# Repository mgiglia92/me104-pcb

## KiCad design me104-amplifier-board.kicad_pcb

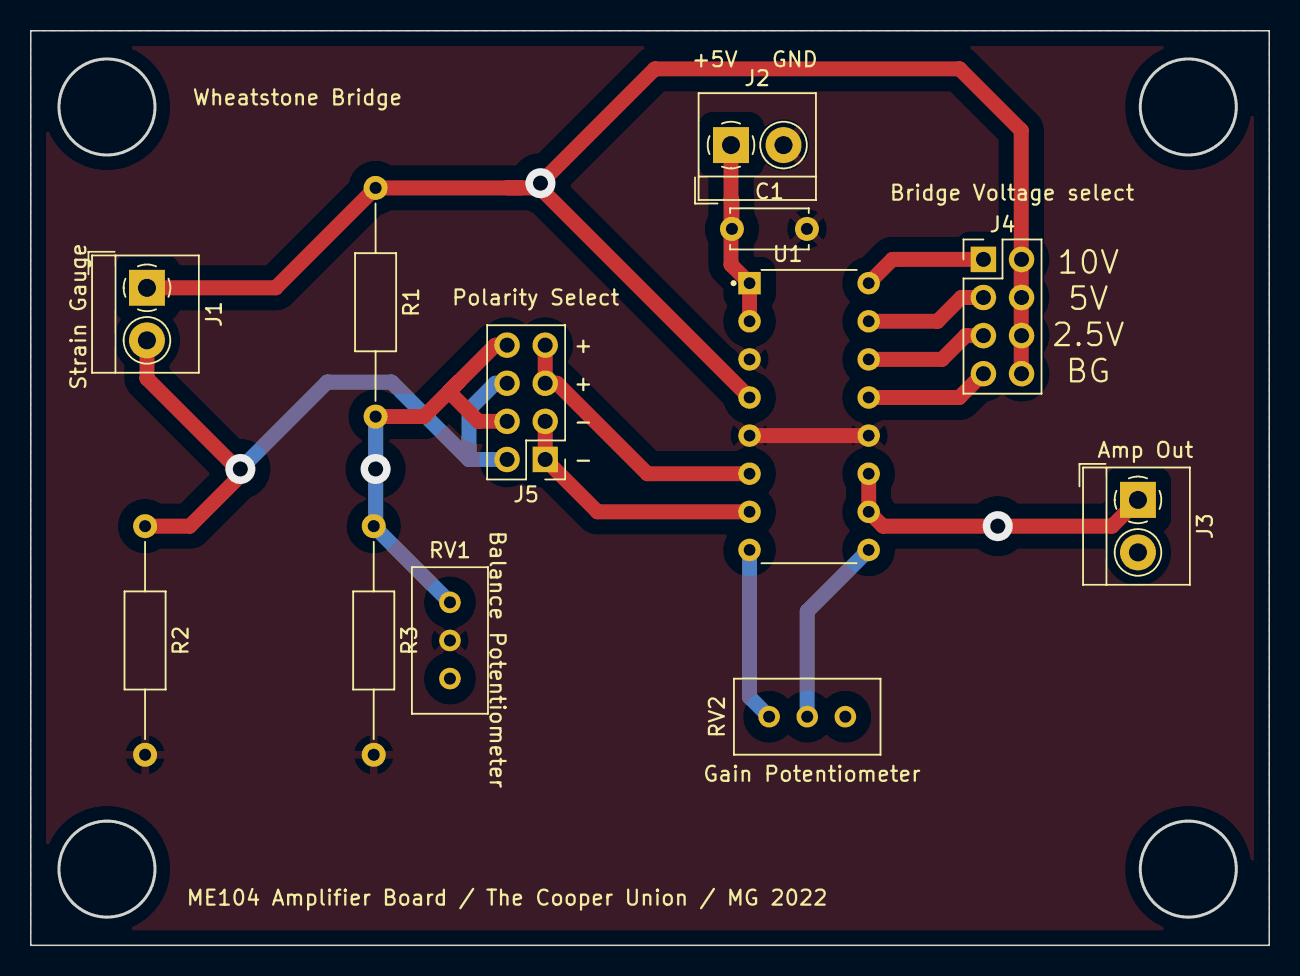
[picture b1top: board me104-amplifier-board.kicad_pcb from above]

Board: 2 copper layers, 82.4 x 60.9 mm, 12 parts (0 on the bottom side), 14 nets.

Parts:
C1: C; C_Disc_D5.0mm_W2.5mm_P5.00mm
J1, J2, J3: Screw_Terminal_strain_gauge; TerminalBlock_4Ucon_1x02_P3.50mm_Horizontal
J4, J5: Conn_02x05_Counter_Clockwise; PinHeader_2x04_P2.54mm_Vertical_EDIT
R1: 120; R_Axial_DIN0207_L6.3mm_D2.5mm_P15.24mm_Horizontal
R2: 5k; R_Axial_DIN0207_L6.3mm_D2.5mm_P15.24mm_Horizontal
R3: 12k; R_Axial_DIN0207_L6.3mm_D2.5mm_P15.24mm_Horizontal
RV1: 10k; Potentiometer_Bourns_3386C_Horizontal
RV2: 1k; Potentiometer_Bourns_3386C_Horizontal
U1: INA125P; DIP794W45P254L1969H508Q16

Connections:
/Amp Out: J3.1, U1.10 (VO), U1.11 (SENSE)
/VIN: C1.1, J2.1, U1.1 (V+), U1.2 (~SLEEP)
GND: C1.2, J2.2, R2.2, R3.2, RV1.2, U1.3 (V-), U1.5 (IAREF), U1.12 (VREFCOM)
unnamed: J1.1, J4.5, J4.6, J4.7, J4.8, R1.1, U1.4 (VREFOUT)
unnamed: J1.2, J5.6, J5.8, R2.1
unnamed: J4.1, U1.16 (VREF10)
unnamed: J4.2, U1.15 (VREF5)
unnamed: J4.3, U1.14 (VREF2.5)
unnamed: J4.4, U1.13 (VREFBG)
unnamed: J5.1, J5.2, U1.7 (V-IN)
unnamed: J5.3, J5.4, U1.6 (V+IN)
unnamed: J5.5, J5.7, R1.2, R3.1, RV1.1
unnamed: RV2.1, U1.8 (RG)
unnamed: RV2.2, U1.9 (RG)
